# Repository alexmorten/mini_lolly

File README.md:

# Mini Lolly

63 WS2812B LEDs on a [Fermat spiral with the golden
angle](https://en.wikipedia.org/wiki/Fermat%27s_spiral#The_golden_ratio_and_the_golden_angle),
driven by an Adafruit Feather ESP32-S2.

```
firmware/     the board firmware (see firmware/README.md)
simulator/    the website — both a browser simulator and the page the device serves
lolly_pcb/    KiCad board generation and the spiral geometry everything else derives from
printing/     diffuser and housing (3MF)
```

## The website

`simulator/index.html` is one self-contained page that does two jobs: it simulates the board
in a browser, and — when it is the copy the firmware serves over its own Wi-Fi AP — it is the
remote control. Pick an effect, tune its parameters, arrange presets, set brightness, export
and import the whole setup.

Open it against a device by joining the AP `MiniLolly Manfred` (password `Lumos2024`) and
visiting <http://192.168.4.1>. It connects to whatever origin served it, so nothing to set up.

The Wi-Fi card in that page hands the board a network of its own to join, after which it lives
at <http://lolly.local> and the AP is gone. Nothing is lost if the join fails or the network
later disappears: the board brings its own AP back up, so the address above always gets you in.

To run it as a plain simulator with no device in reach, serve the repo and open it — it falls
back to a local preset list and says so:

```bash
python3 -m http.server 8000
```

Then <http://localhost:8000/simulator/>. To point a locally-opened page at a real board,
type its address into **Device URL** and press **Connect** (the firmware answers CORS
preflights, so this works cross-origin).

The device's own copy is baked into the firmware image, so changes here only reach the board
through `firmware/scripts/prepare_data.sh` and a flash.

## Firmware

See [firmware/README.md](firmware/README.md) for effects, the preset model, the REST API and
the build. In short:

```bash
cd firmware
./scripts/prepare_data.sh    # pack simulator/ into include/spa_gz.h
pio run -t upload
./test/run.sh                # off-device checks, no board needed
```

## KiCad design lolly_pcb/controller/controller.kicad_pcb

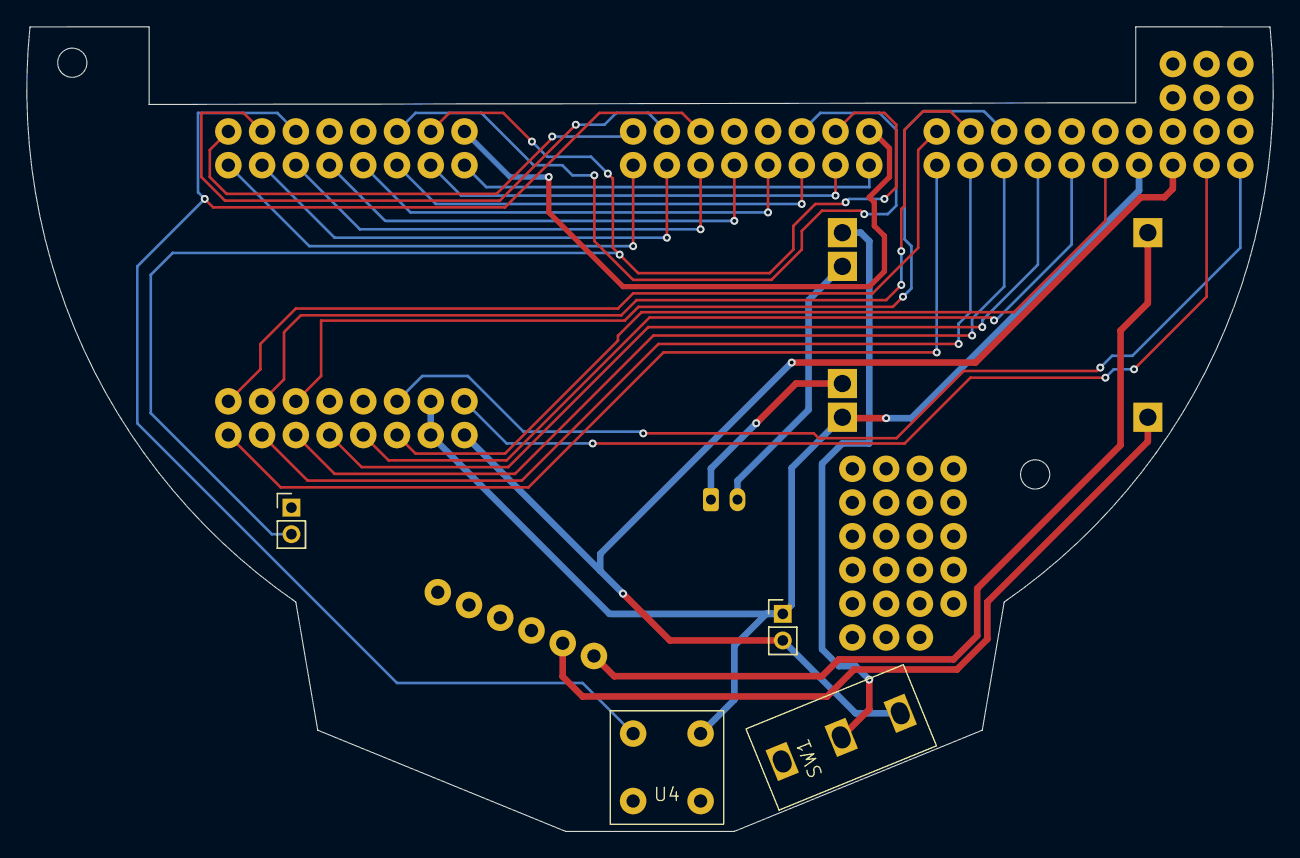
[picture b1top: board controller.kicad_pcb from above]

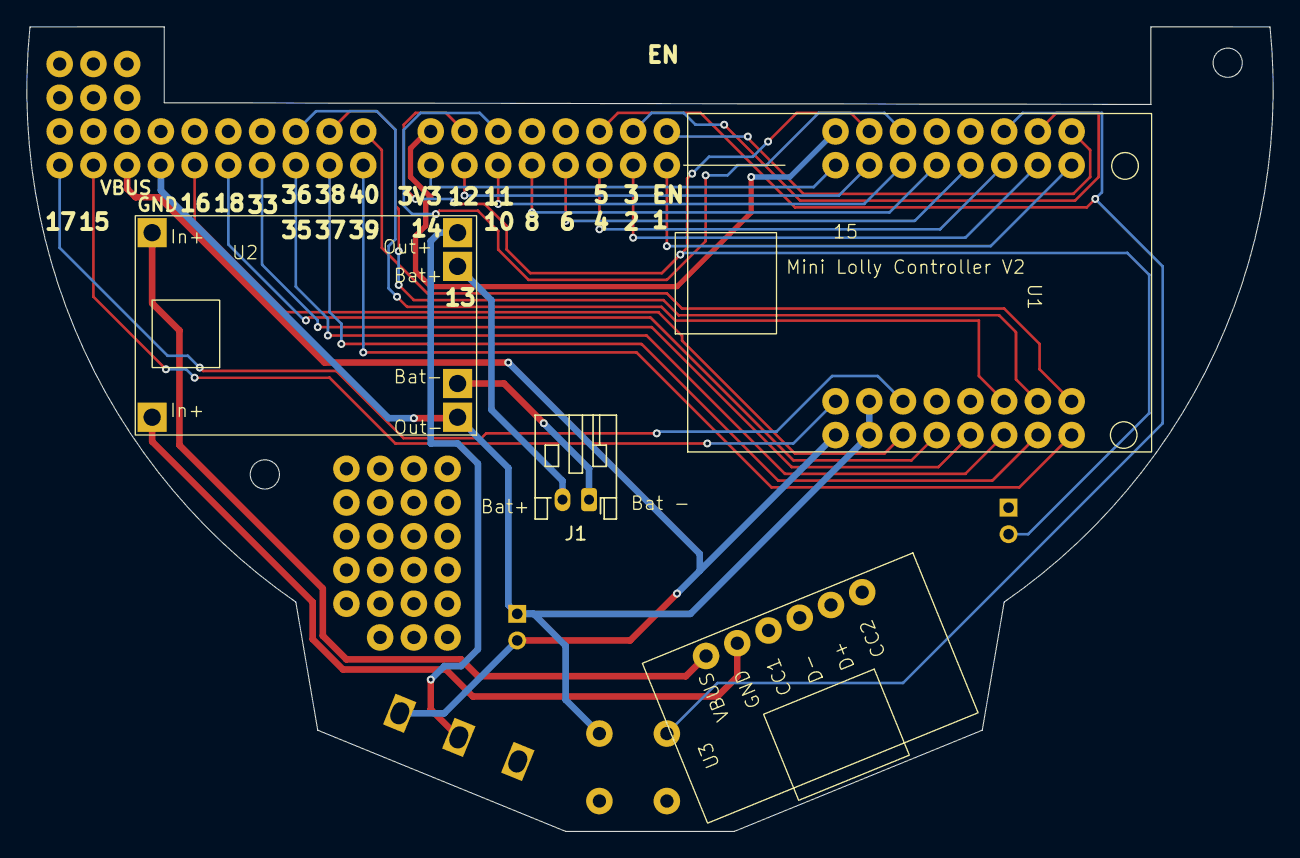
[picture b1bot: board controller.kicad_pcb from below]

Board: 2 copper layers, 93.8 x 60.6 mm, 6 parts (4 on the bottom side), 8 nets.

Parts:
J1: Conn_01x02_Pin; JST_PH_S2B-PH-K_1x02_P2.00mm_Horizontal
SW1: SW_SPDT; 1P2T SPDT RUNCCI-YUN
U1: ESP32-S2-MINI-1; esp32 s2-mini dev board
U2: tp4056 module
U3: usb-c 5v breakout
U4: small thoughhole button

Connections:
5: U1.5 (GPIO5/ADC1_CH4), U4.1 (In1)
Bat+: J1.2, U2.5 (Bat_+)
Bat-: J1.1, U2.6 (Bat_-)
GND: U1.GND, U2.4 (Out_-), U4.3 (Out1)
unnamed: SW1.2 (B), U2.3 (Out_+)
unnamed: U2.1 (In_+), U3.1 (VBUS)
unnamed: U2.2 (In_-), U3.2 (GND)
VBUS: SW1.3 (C), U1.VBUS

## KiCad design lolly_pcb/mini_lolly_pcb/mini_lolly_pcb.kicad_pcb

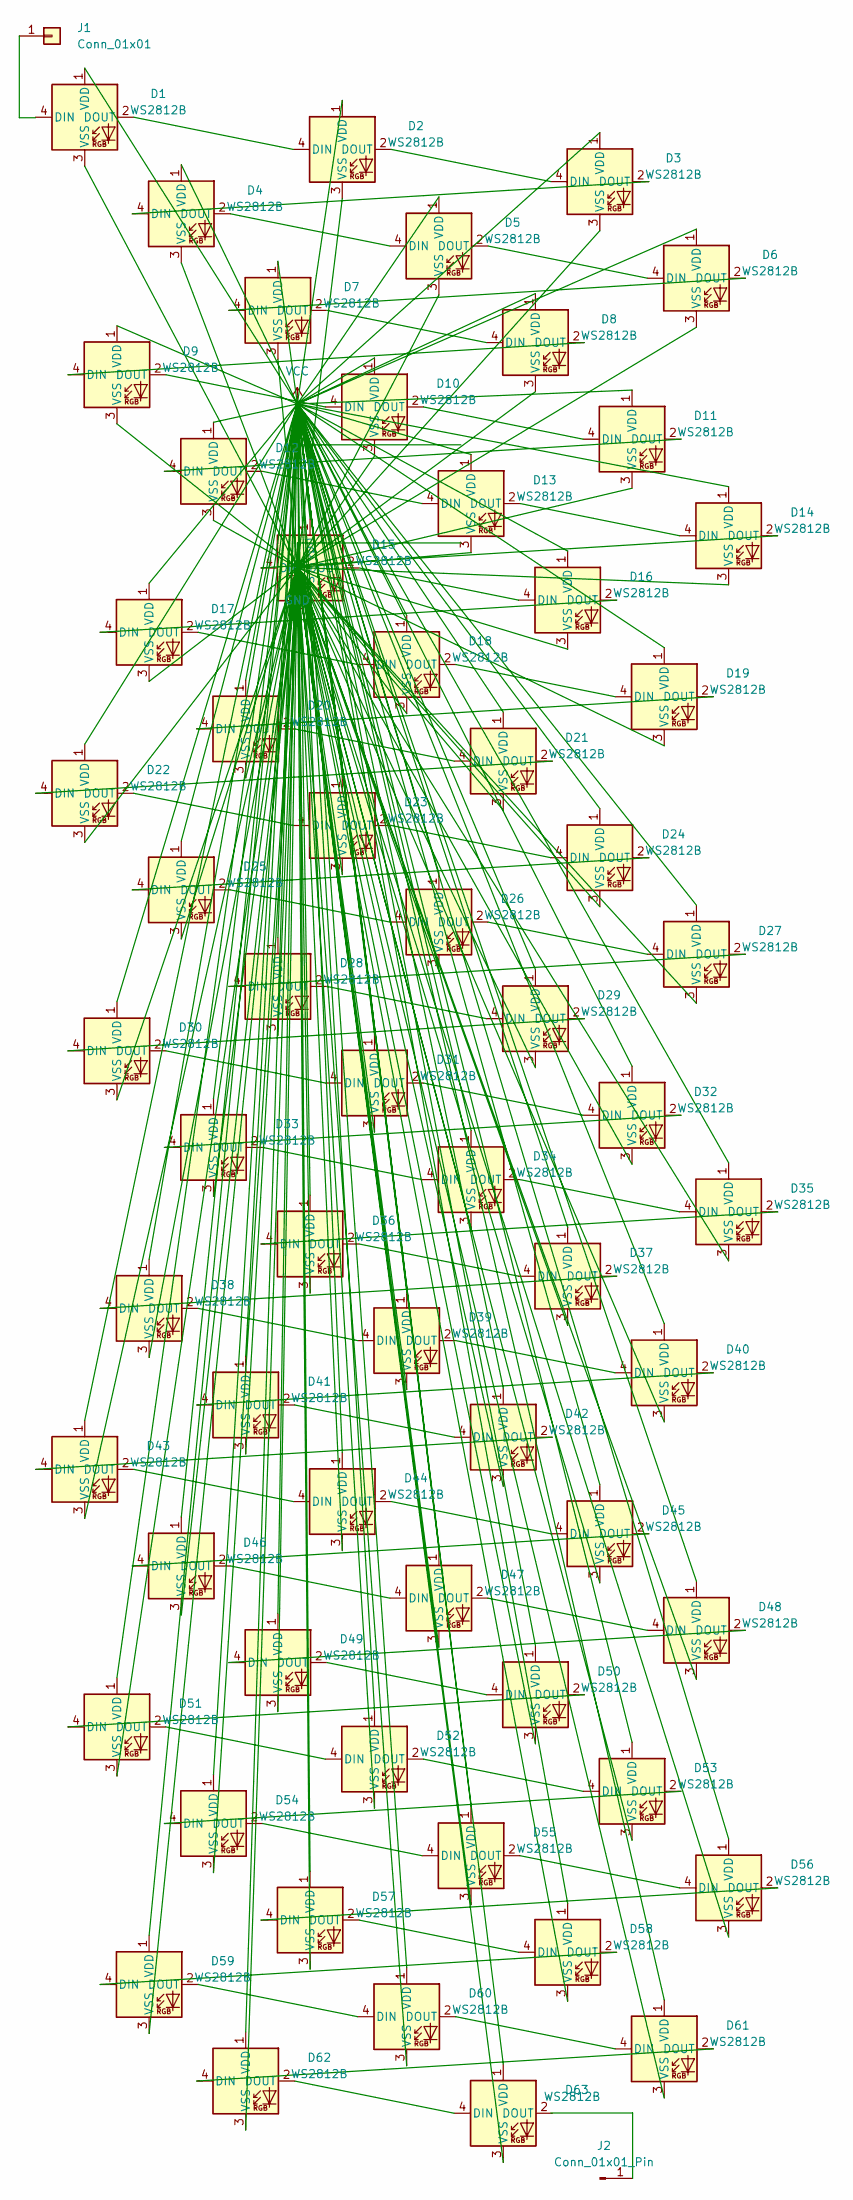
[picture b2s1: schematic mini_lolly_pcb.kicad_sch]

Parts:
D1, D2, D3, D4, D5, D6, D7, D8, D9, D10, D11, D12, D13, D14, D15, D16, D17, D18, D19, D20, D21, D22, D23, D24, D25, D26, D27, D28, D29, D30, D31, D32, D33, D34, D35, D36, D37, D38, D39, D40, D41, D42, D43, D44, D45, D46, D47, D48, D49, D50, D51, D52, D53, D54, D55, D56, D57, D58, D59, D60, D61, D62, D63: WS2812B; LED_WS2812B_PLCC4_5.0x5.0mm_P3.2mm
J1: Conn_01x01
J2: Conn_01x01_Pin

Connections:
unnamed: D1.2 (DOUT), D2.4 (DIN)
unnamed: D2.2 (DOUT), D3.4 (DIN)
unnamed: D3.2 (DOUT), D4.4 (DIN)
unnamed: D4.2 (DOUT), D5.4 (DIN)
unnamed: D5.2 (DOUT), D6.4 (DIN)
unnamed: D6.2 (DOUT), D7.4 (DIN)
unnamed: D7.2 (DOUT), D8.4 (DIN)
unnamed: D8.2 (DOUT), D9.4 (DIN)
unnamed: D9.2 (DOUT), D10.4 (DIN)
unnamed: D10.2 (DOUT), D11.4 (DIN)
unnamed: D11.2 (DOUT), D12.4 (DIN)
unnamed: D12.2 (DOUT), D13.4 (DIN)
unnamed: D13.2 (DOUT), D14.4 (DIN)
unnamed: D14.2 (DOUT), D15.4 (DIN)
unnamed: D15.2 (DOUT), D16.4 (DIN)
unnamed: D16.2 (DOUT), D17.4 (DIN)
unnamed: D17.2 (DOUT), D18.4 (DIN)
unnamed: D18.2 (DOUT), D19.4 (DIN)
unnamed: D19.2 (DOUT), D20.4 (DIN)
unnamed: D20.2 (DOUT), D21.4 (DIN)
unnamed: D21.2 (DOUT), D22.4 (DIN)
unnamed: D22.2 (DOUT), D23.4 (DIN)
unnamed: D23.2 (DOUT), D24.4 (DIN)
unnamed: D24.2 (DOUT), D25.4 (DIN)
unnamed: D25.2 (DOUT), D26.4 (DIN)
unnamed: D26.2 (DOUT), D27.4 (DIN)
unnamed: D27.2 (DOUT), D28.4 (DIN)
unnamed: D28.2 (DOUT), D29.4 (DIN)
unnamed: D29.2 (DOUT), D30.4 (DIN)
unnamed: D30.2 (DOUT), D31.4 (DIN)
unnamed: D31.2 (DOUT), D32.4 (DIN)
unnamed: D32.2 (DOUT), D33.4 (DIN)
unnamed: D33.2 (DOUT), D34.4 (DIN)
unnamed: D34.2 (DOUT), D35.4 (DIN)
unnamed: D35.2 (DOUT), D36.4 (DIN)
unnamed: D36.2 (DOUT), D37.4 (DIN)
unnamed: D37.2 (DOUT), D38.4 (DIN)
unnamed: D38.2 (DOUT), D39.4 (DIN)
unnamed: D39.2 (DOUT), D40.4 (DIN)
unnamed: D40.2 (DOUT), D41.4 (DIN)
unnamed: D41.2 (DOUT), D42.4 (DIN)
unnamed: D42.2 (DOUT), D43.4 (DIN)
unnamed: D43.2 (DOUT), D44.4 (DIN)
unnamed: D44.2 (DOUT), D45.4 (DIN)
unnamed: D45.2 (DOUT), D46.4 (DIN)
unnamed: D46.2 (DOUT), D47.4 (DIN)
unnamed: D47.2 (DOUT), D48.4 (DIN)
unnamed: D48.2 (DOUT), D49.4 (DIN)
unnamed: D49.2 (DOUT), D50.4 (DIN)
unnamed: D50.2 (DOUT), D51.4 (DIN)
unnamed: D51.2 (DOUT), D52.4 (DIN)
unnamed: D52.2 (DOUT), D53.4 (DIN)
unnamed: D53.2 (DOUT), D54.4 (DIN)
unnamed: D54.2 (DOUT), D55.4 (DIN)
unnamed: D55.2 (DOUT), D56.4 (DIN)
unnamed: D56.2 (DOUT), D57.4 (DIN)
unnamed: D57.2 (DOUT), D58.4 (DIN)
unnamed: D58.2 (DOUT), D59.4 (DIN)
unnamed: D59.2 (DOUT), D60.4 (DIN)
unnamed: D60.2 (DOUT), D61.4 (DIN)
unnamed: D61.2 (DOUT), D62.4 (DIN)
unnamed: D62.2 (DOUT), D63.4 (DIN)

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
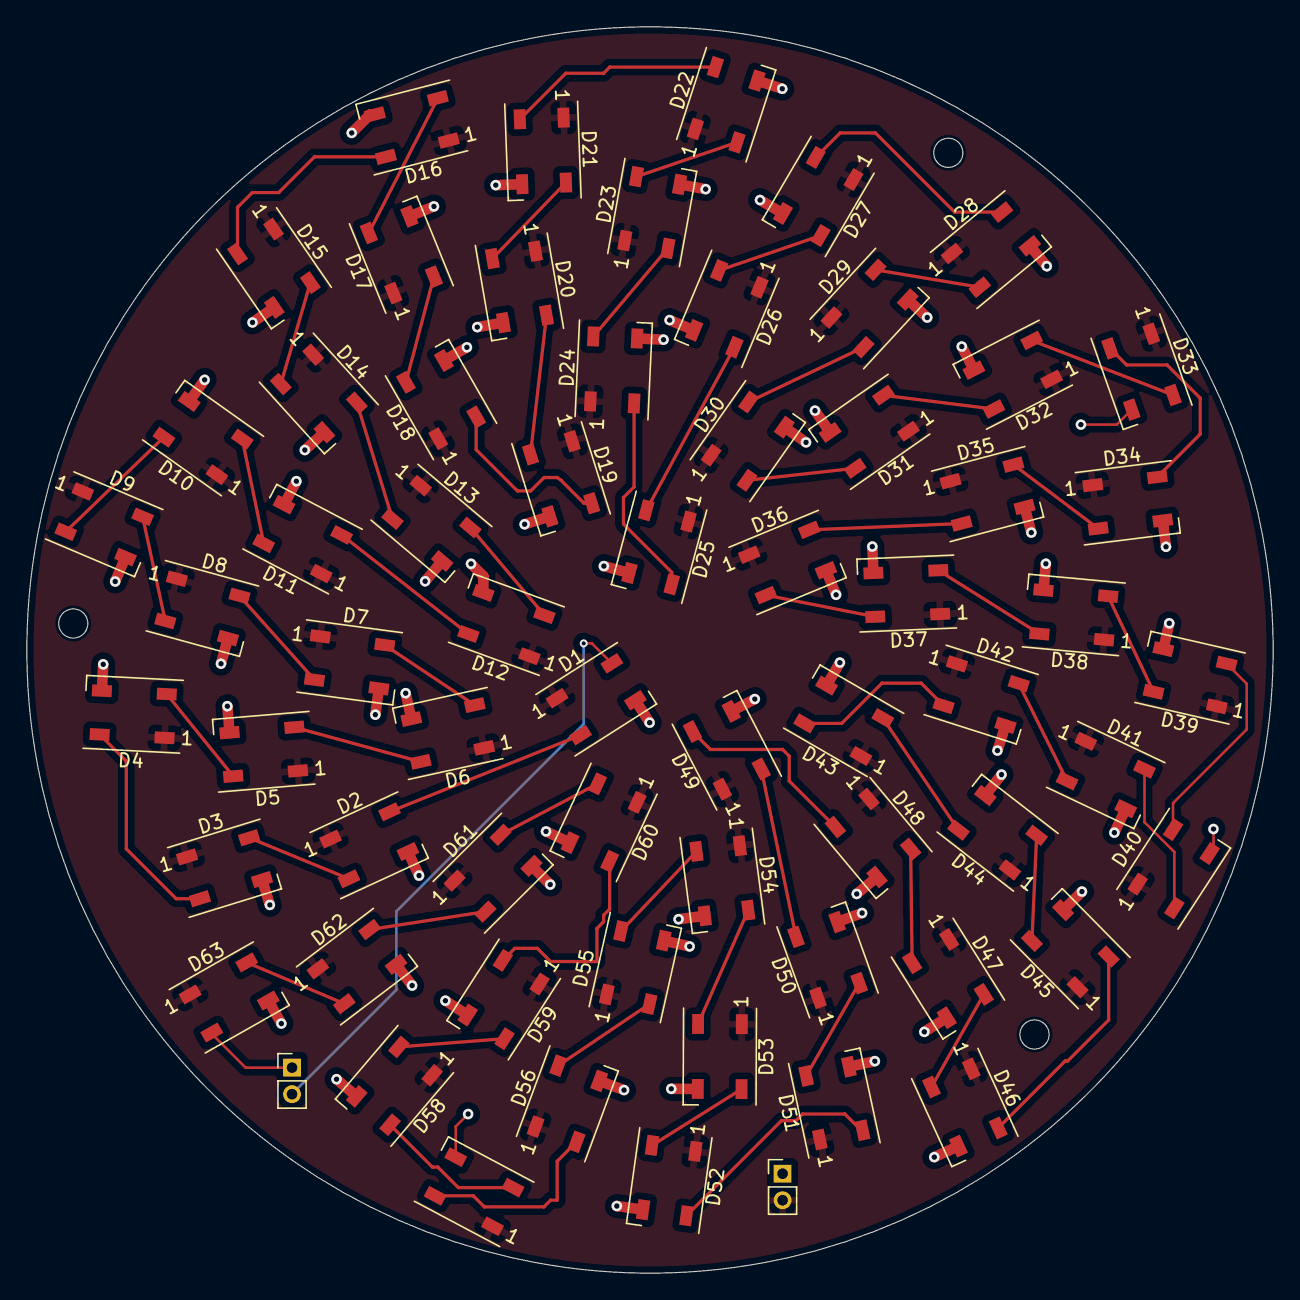
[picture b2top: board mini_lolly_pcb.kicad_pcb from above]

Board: 2 copper layers, 94.0 x 94.0 mm, 63 parts (0 on the bottom side), 64 nets.

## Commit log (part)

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2024-07-24 init commit
2024-07-24 add tracks and vias
2024-07-24 somewhat working version
2024-07-25 remove backup files
2024-07-25 rotate outermost leds for space
2024-07-26 add HTML canvas lolly simulator (so far only draws blurred static LEDs)
2024-07-26 apply clipping and brightness filter for lighter colors
2024-07-26 first color animation of mini lolly
2024-07-27 match the p5js sketch of @dynamix with the simulator, but it is pretty slow (~13 fps on M1 Pro)
2024-07-27 improve FPS display
2024-07-27 fix blurry LED drawing performance problem, back at smooth 120FPS (frame time 2.5ms on M1 Pro)
2024-07-27 also allow simulating the big 512 LED lolly
2024-07-27 add esp32 s3-mini as controller
2024-07-27 add charging circuit, connector and switch
2024-07-27 make animation pausable (laptop battery thanks you)
2024-07-27 first proper layout
    includes solder pads for later components, better antenna placement, and routing
2024-07-27 better board outline
2024-07-27 add image mapping capability
2024-07-27 add rotation animation to the image mapper
2024-07-29 fix missing connection
2024-08-03 add proper usb-c 5v breakdout board
    the charging circuit does not have the pull down resistors on the proper pins to get 5v from usb-c PD
2024-08-03 rearrange board for usb-c breakout board
2024-08-03 add super simple test firmware
2024-08-03 add labels
2024-08-03 fix label too close to hole
2024-08-04 use pin no. 5 for button
2024-08-06 add basic mapping test
2024-08-06 change from 2 space indentation to 4 space tabs with no JS semicolons
2024-08-06 add more structure in the simulator
2024-08-06 implement color rings demo from current controller firmware
2024-08-06 add control CSS layout with pattern switcher
2024-08-06 add parameters UI
2024-08-08 fix controller hole positions and sizes
2024-08-12 join twinkle fox example and color ring demo, cycle them with the board button (pin 0)
2024-08-12 switch to different board, so that hands free programming works
2024-08-12 add a WIFI AP with a web server that can switch between patterns
2024-08-19 add Fire2012 example
2024-08-19 add Cylon FastLED example
2024-08-19 DRY up pattern UI code
2024-08-19 add all DemoReel100 patterns
2024-08-20 nicer UI HTML with more compact pattern button layout
2024-08-21 add physical button to pattern switching, disable Cylon because it doesn't have a fast loop
2024-08-21 move lolly specific SSID data to top of file
2025-07-09 extract animations to dedicated files
2025-07-09 use led_config
2025-07-09 fix pin
2025-07-09 add polar rings
2026-05-14 add brightness controls
2026-05-14 ignore some firmware paths
2026-05-14 update pcb files
2026-05-14 add printing files
